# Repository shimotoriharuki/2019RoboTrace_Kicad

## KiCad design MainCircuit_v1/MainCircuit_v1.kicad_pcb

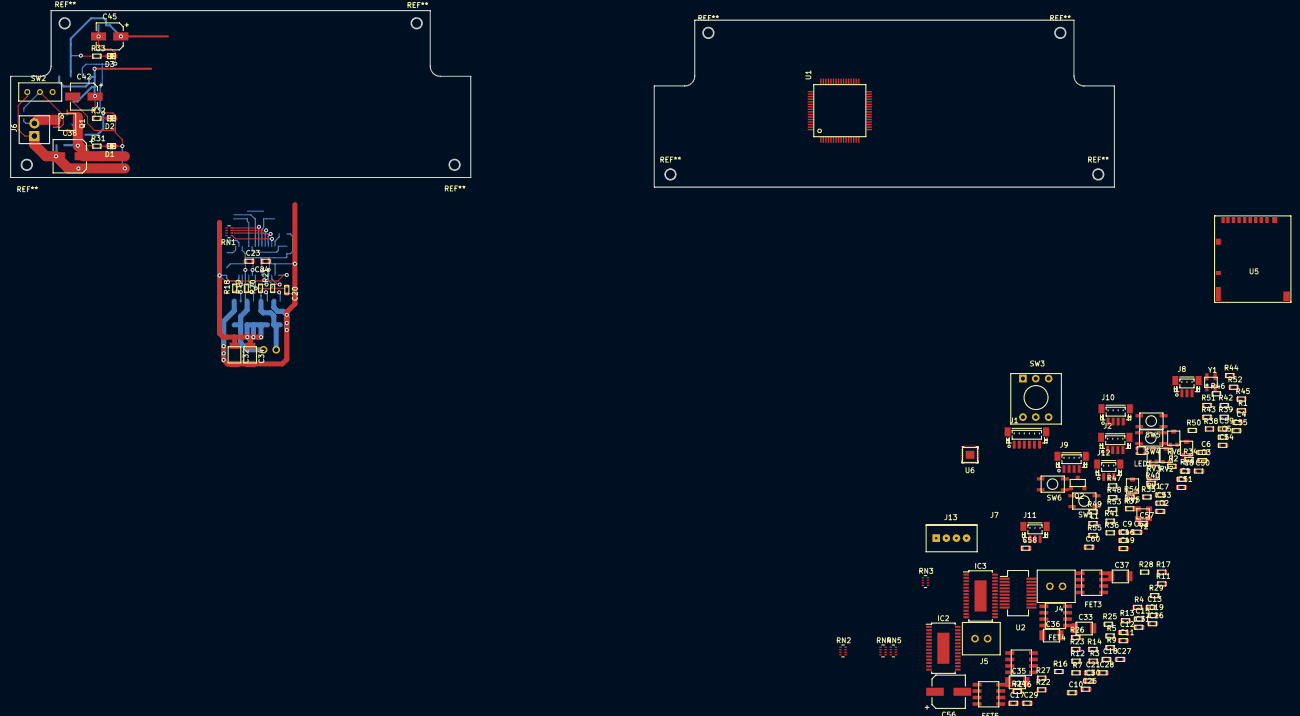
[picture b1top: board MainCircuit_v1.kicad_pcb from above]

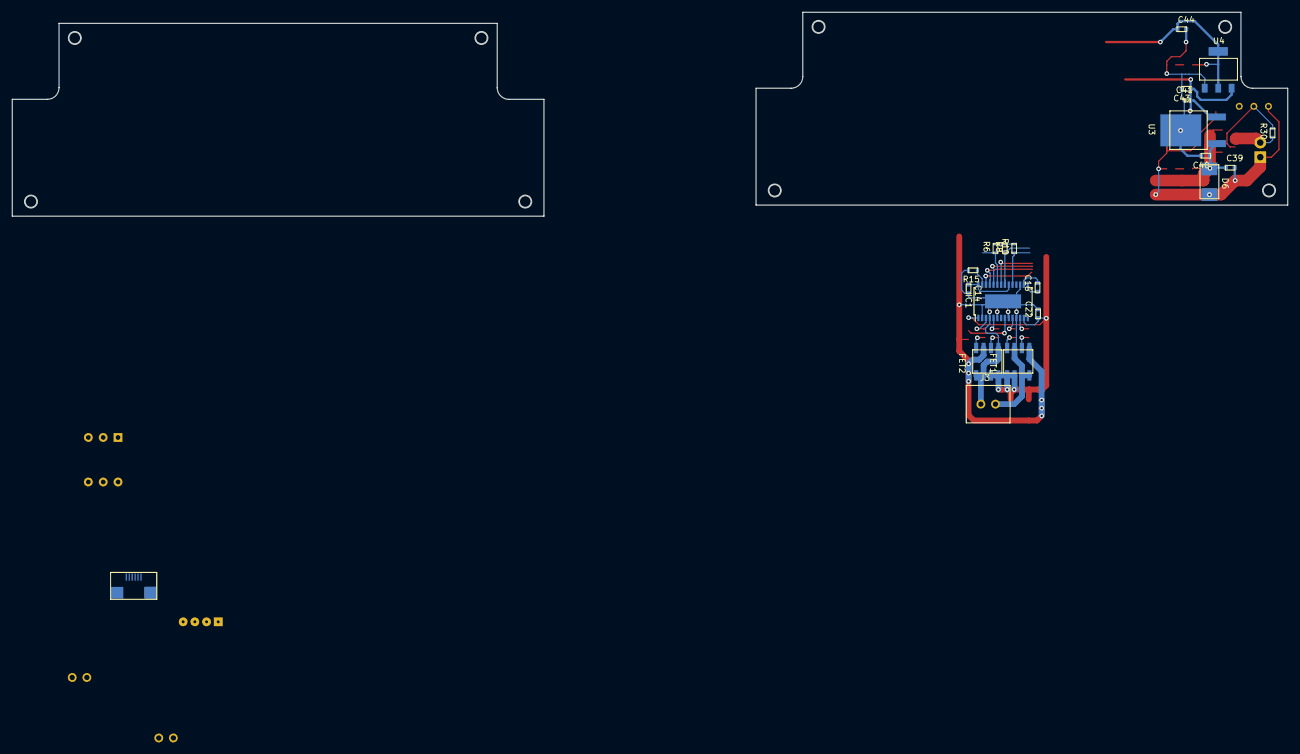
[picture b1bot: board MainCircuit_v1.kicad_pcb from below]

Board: 2 copper layers, 218.3 x 34.9 mm, 168 parts (20 on the bottom side), 139 nets.

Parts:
C1, C3, C4, C5, C6, C8, C9, C10, C11, C12, C13, C14, C15, C18, C52, C54, C55, C57, C58, C59, C60: 0.1u; C_1608_HandSolderring
C2, C39, C43, C44, C49, C50, C51: 1u; C_1608_HandSolderring
C7: 4.7u; C_1608_HandSolderring
C16, C17, C19: 470n; C_1608_HandSolderring
C20, C21, C23, C24, C26, C27, C28, C30, C31: 0.22u; C_1608_HandSolderring
C22, C25, C29: 10u; C_1608_HandSolderring
C32, C33, C34, C35, C36, C37: 47u; c_3225
C38, C56: 180u; CP_Elec_6.3x5.8
C40: 0.39u; C_1608_HandSolderring
C41: 2.2u; c_1005
C42, C45: 82u; CP_Elec_5x5.8
C46: 0.1; C_1608_HandSolderring
C53: 0.1U; C_1608_HandSolderring
D1, D2, D3: LED; LED 1608
D6: 1SMB5930BT3G
FET1, FET2, FET3, FET4, FET5, FET6: IRF8915
IC1, IC2, IC3: A3921; TSSOP-28-1EP_4.4x9.7mm_Pitch0.65mm
J1: SH; JST_SH_BM06B-SRSS-TB_06x1.00mm_Straight
J2, J9, J10: SH; JST_SH_BM04B-SRSS-TB_04x1.00mm_Straight
J3, J4, J5: XA; XA_top_2pin
J6: ILG; ILG_2pin
J7: FFC; CN-FFC-(0.5)6PD
J8, J11, J12: SH; JST_SH_BM03B-SRSS-TB_03x1.00mm_Straight
J13: PA; PA_4pin
L1: 330; R_1608_HandSoldering
LED1: OSTB0603C1C-A
Q1: μPA2815T1S; uPA2815T1S
Q2: DMG3415U
R1: 150k; R_1608_HandSoldering
R2, R3, R4, R5, R6, R7, R8, R9, R10, R11, R12, R13, R14, R34, R35, R36, R37, R38, R39, R43, R45, R47, R53, R54: 10k; R_1608_HandSoldering
R15, R16, R17: 3k; R_1608_HandSoldering
R18, R19, R20, R21, R22, R23, R24, R25, R26, R27, R28, R29: 75; R_1608_HandSoldering
R30: 12K; R_1608_HandSoldering
R31: 1k; R_1608_HandSoldering
R32: 560; R_1608_HandSoldering
R33: 270; R_1608_HandSoldering
R40, R41, R42: 47K; R_1608_HandSoldering
R44, R46, R48: 100; R_1608_HandSoldering
R49: 1.2k; R_1608_HandSoldering
R50: 680; R_1608_HandSoldering
R51: 470; R_1608_HandSoldering
R52: 39; R_1608_HandSoldering
R55: 10K; R_1608_HandSoldering
RN1, RN2, RN3, RN4, RN5: 10k; my_RN
RV1, RV2, RV3, RV4, RV5, RV6: 1k; ST2TA
SW1, SW4, SW5, SW6: SKRPACE010
SW2: SS12D01G4
SW3: ERD216RSZ; rotary_switch
U1: STM32F446RE; stm32f401
U2: ADuM7640; ADUM7640ARQZ
U3: NJM2845; NJM2845DL1
U4: ADP3338; SOT-223
U5: SD_SLOT; micro_SDcard
U6: ICM20648
Y1: ASDMB-8.000MHZ-LY-T
Y2: TC25L5I32K7680

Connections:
+3V3: C1.1, C3.1, C5.2, C6.1, C8.1, C9.1, C10.1, C11.1, C12.1, C13.1, C44.1, C45.1, C46.1, C52.1, C54.1, C55.1, C57.1, C59.1, J1.1, J2.1, J12.1, J13.1, L1.2, LED1.1, Q2.1, R1.1, R33.1, R34.1, R35.1, R36.1, R37.1, R38.1, R39.1, R40.1, R41.1, R42.1, R43.1, R45.1, R47.1, R53.1, R54.1, R55.1, RN1.5, RN1.6, RN1.7, RN1.8, RN2.5, RN2.6, RN2.7, RN2.8, RN3.5, RN3.6, RN3.7, RN3.8, RN4.5, RN4.6, RN4.7, RN4.8, U1.1, U1.19, U1.32, U1.48, U1.64, U2.1, U2.7, U2.14, U2.20, U4.2, U5.4, U6.8, U6.13, Y1.4, Y2.1, Y2.4
+5V: C41.1, C42.1, C43.1, C58.1, C60.1, J9.1, J10.1, R32.1, RN5.5, RN5.6, RN5.7, RN5.8, U3.3, U4.3
+BATT: C22.1, C25.1, C29.1, C32.1, C33.1, C34.1, C35.1, C36.1, C37.1, C38.1, C39.1, C40.1, C56.1, D6.1, FET1.5, FET1.6, FET2.7, FET2.8, FET3.5, FET3.6, FET4.7, FET4.8, FET5.5, FET5.6, FET6.7, FET6.8, IC1.1, IC1.13, IC2.1, IC2.13, IC3.1, IC3.13, Q1.3, R31.1, U3.1
CS_IMU: RN4.1, U1.54, U6.22
CS_SD: U1.50, U5.2
DIR_MAXON1: IC1.19, R10.1, U1.40
DIR_MAXON2: IC2.19, R11.1, U1.36
DIR_VCM: R5.1, U1.45, U2.3
ENCORDER_1A: J9.2, RN5.1, U1.14
ENCORDER_1B: J9.3, RN5.2, U1.15
ENCORDER_2A: J10.2, RN5.4, U1.58
ENCORDER_2B: J10.3, RN5.3, U1.59
GND: C1.2, C2.2, C3.2, C4.1, C5.1, C6.2, C7.2, C8.2, C9.2, C10.2, C11.2, C12.2, C13.2, C14.2, C15.2, C18.2, C20.2, C21.2, C22.2, C25.2, C28.2, C29.2, C32.2, C33.2, C34.2, C35.2, C36.2, C37.2, C38.2, C39.2, C40.2, C41.2, C42.2, C43.2, C44.2, C45.2, C46.2, C49.2, C50.2, C51.2, C52.2, C56.2, C57.2, C58.2, C59.2, C60.2, D1.1, D2.1, D3.1, D6.2, FET1.1, FET2.3, FET3.1, FET4.3, FET5.1, FET6.3, IC1.2, IC1.17, IC1.29, IC2.2, IC2.17, IC2.29, IC3.2, IC3.17, IC3.29, J1.3, J2.4, J6.1, J7.6, J8.3, J9.4, J10.4, J11.3, J12.3, J13.4, R2.1, R3.2, R4.2, R5.2, R6.2, R7.2, R8.2, R9.2, R10.2, R11.2, R12.2, R13.2, R14.2, R15.2, R16.2, R17.2, SW1.1, SW2.3, SW3.C, SW4.2, SW5.2, SW6.2, U1.12, U1.18, U1.31, U1.47, U1.63, U2.2, U2.10, U2.19, U3.2, U4.1, U5.6, U5.9, U5.11, U6.11, U6.18, U6.20, Y1.2, Y2.2
INSERT_SD: R41.2, U1.2, U5.10
LED_B: R51.2, U1.28
LED_G: R50.2, U1.33
LED_R: R49.2, U1.34
LINE_SENSOR1: J7.2, RV1.1, U1.26
LINE_SENSOR2: J7.3, RV2.1, U1.25
LINE_SENSOR3: J7.4, RV3.1, U1.24
LINE_SENSOR4: J7.5, RV4.1, U1.23
LINE_SENSOR5: J8.2, RV5.1, U1.22
LINE_SENSOR6: J11.2, RV6.1, U1.21
MISO_IMU: RN4.4, U1.56, U6.9
MISO_SD: U1.52, U5.7
MOSI_IMU: RN4.3, U1.57, U6.24
MOSI_SD: U1.53, U5.3
NRST: C2.1, J1.5, R1.2, SW1.2, U1.7
unnamed: C4.2, L1.1, U1.13
unnamed: C7.1, U1.30
unnamed: C14.1, IC1.20, IC1.28
unnamed: C15.1, IC2.20, IC2.28
unnamed: C16.1, IC1.15
unnamed: C16.2, IC1.16
unnamed: C17.1, IC2.15
unnamed: C17.2, IC2.16
unnamed: C18.1, IC3.20, IC3.28
unnamed: C19.1, IC3.15
unnamed: C19.2, IC3.16
unnamed: C20.1, IC1.8
unnamed: C21.1, IC2.8
unnamed: C23.1, FET1.3, FET1.7, FET1.8, IC1.11, J3.1
unnamed: C23.2, IC1.9
unnamed: C24.1, FET2.1, FET2.5, FET2.6, IC1.4, J3.2
unnamed: C24.2, IC1.6
unnamed: C26.1, FET3.3, FET3.7, FET3.8, IC2.11, J4.1
unnamed: C26.2, IC2.9
unnamed: C27.1, FET4.1, FET4.5, FET4.6, IC2.4, J4.2
unnamed: C27.2, IC2.6
unnamed: C28.1, IC3.8
unnamed: C30.1, FET5.3, FET5.7, FET5.8, IC3.11, J5.1
unnamed: C30.2, IC3.9
unnamed: C31.1, FET6.1, FET6.5, FET6.6, IC3.4, J5.2
unnamed: C31.2, IC3.6
unnamed: C53.1, U6.10
unnamed: C53.2, C54.2, C55.2
unnamed: D1.2, R31.2
unnamed: D2.2, R32.2
unnamed: D3.2, R33.2
unnamed: FET1.2, R18.1
unnamed: FET1.4, R19.1
unnamed: FET2.2, R20.1
unnamed: FET2.4, R21.1
unnamed: FET3.2, R22.1
unnamed: FET3.4, R23.1
unnamed: FET4.2, R24.1
unnamed: FET4.4, R25.1
unnamed: FET5.2, R26.1
unnamed: FET5.4, R27.1
unnamed: FET6.2, R28.1
unnamed: FET6.4, R29.1
unnamed: IC1.3, R21.2
unnamed: IC1.5, R20.2
unnamed: IC1.10, R19.2
unnamed: IC1.12, R18.2
unnamed: IC1.22, RN1.4
unnamed: IC1.24, RN1.3
unnamed: IC1.25, RN1.2
unnamed: IC1.26, RN1.1
unnamed: IC1.27, R15.1
unnamed: IC2.3, R25.2
unnamed: IC2.5, R24.2
unnamed: IC2.10, R23.2
unnamed: IC2.12, R22.2
unnamed: IC2.22, RN2.4
unnamed: IC2.24, RN2.3
unnamed: IC2.25, RN2.2
unnamed: IC2.26, RN2.1
unnamed: IC2.27, R16.1
unnamed: IC3.3, R29.2
unnamed: IC3.5, R28.2
unnamed: IC3.10, R27.2
unnamed: IC3.12, R26.2
unnamed: IC3.19, R14.1, U2.18
unnamed: IC3.21, R13.1, U2.17
unnamed: IC3.22, RN3.4
unnamed: IC3.23, R12.1, U2.16
unnamed: IC3.24, RN3.3
unnamed: IC3.25, RN3.2
unnamed: IC3.26, RN3.1
unnamed: IC3.27, R17.1
unnamed: J6.2, Q1.1, R30.1
unnamed: J7.1, J8.1, J11.1, Q2.3
unnamed: LED1.2, R49.1
unnamed: LED1.3, R51.1
unnamed: LED1.4, R50.1
unnamed: Q1.2, R30.2, SW2.2
unnamed: Q2.2, R52.1, R55.2
unnamed: R2.2, U1.60
unnamed: R40.2, U5.8
unnamed: R42.2, U5.1
unnamed: R44.1, SW4.1
unnamed: R46.1, SW5.1
unnamed: R48.1, SW6.1
OSC_IN: U1.5, Y1.3
POT: J12.2, U1.27
PWM_MAXON1: IC1.23, R6.1, U1.38
PWM_MAXON2: IC2.23, R7.1, U1.37
PWM_VCM: R3.1, U1.44, U2.5
RTC_IN: U1.3, Y2.3
RX: J2.2, U1.43
R_SW1: SW3.1, U1.8
R_SW2: SW3.2, U1.9
R_SW4: SW3.4, U1.10
R_SW8: SW3.8, U1.11
SCK_IMU: RN4.2, U1.55, U6.23
SCK_SD: U1.51, U5.5
SCL_LCD: J13.2, R53.2, U1.61
SDA_LCD: J13.3, R54.2, U1.62
SENSOR_PULS_PWM: R52.2, U1.29
SR_MAXON1: IC1.21, R8.1, U1.39
SR_MAXON2: IC2.21, R9.1, U1.35
SR_VCM: R4.1, U1.41, U2.4
SW1: C49.1, R43.2, R44.2, U1.16
SW2: C50.1, R45.2, R46.2, U1.17
SW3: C51.1, R47.2, R48.2, U1.20
TCK: J1.2, U1.49
TMS: J1.4, U1.46
TX: J2.3, U1.42

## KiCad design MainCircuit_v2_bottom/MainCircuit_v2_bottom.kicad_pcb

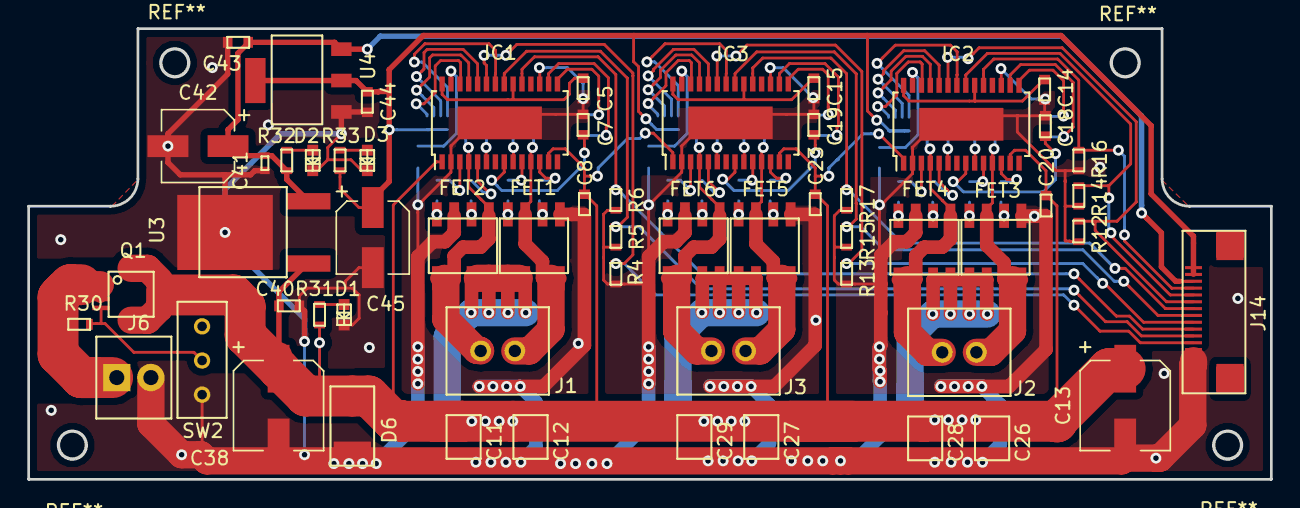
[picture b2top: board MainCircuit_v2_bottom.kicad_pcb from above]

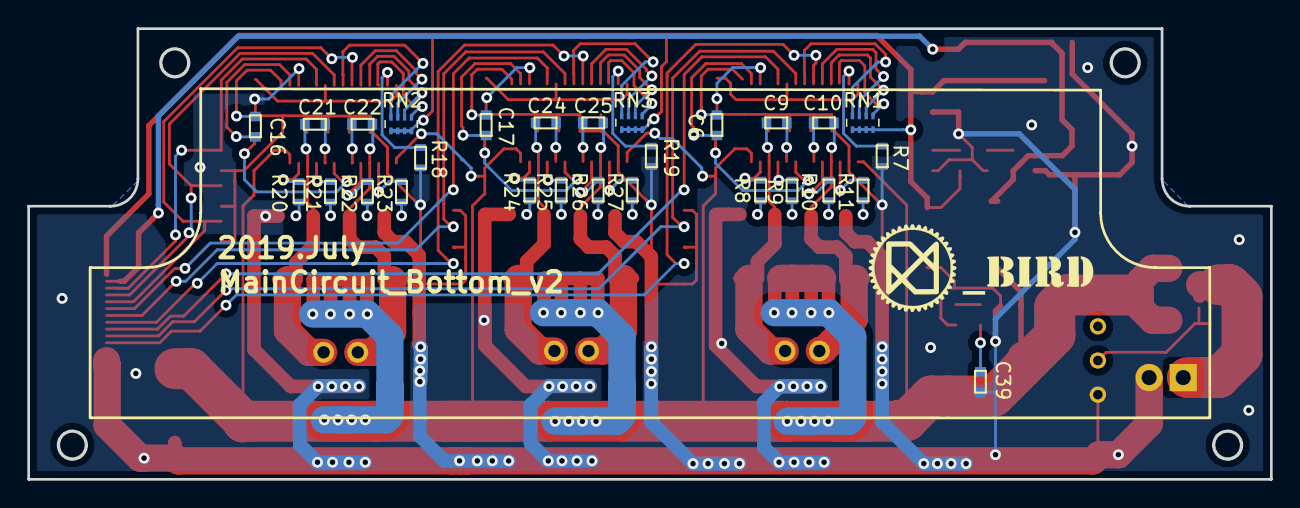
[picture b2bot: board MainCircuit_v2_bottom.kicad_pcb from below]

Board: 2 copper layers, 91.0 x 33.0 mm, 86 parts (29 on the bottom side), 81 nets.

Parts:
C5, C14, C15: 0.1u; C_1608_HandSolderring
C6, C16, C17: 470n; C_1608_HandSolderring
C7, C9, C10, C18, C19, C21, C22, C24, C25: 0.22u; C_1608_HandSolderring
C8, C20, C23: 10u; C_1608_HandSolderring
C11, C12, C26, C27, C28, C29: 47u; c_3225
C13, C38: 180u; CP_Elec_6.3x5.8
C39, C43, C44: 1u; C_1608_HandSolderring
C40: 0.39u; C_1608_HandSolderring
C41: 2.2u; c_1005
C42, C45: 82u; CP_Elec_5x5.8
D1, D2, D3: LED; LED 1608
D6: 1SMB5930BT3G
FET1, FET2, FET3, FET4, FET5, FET6: IRF8915
IC1, IC2, IC3: A3921; TSSOP-28-1EP_4.4x9.7mm_Pitch0.65mm
J1, J2, J3: XA; XA_top_2pin
J6: ILG; ILG_2pin
J14: FFC_to_top; CN-FFC-SMT2(CN-FFC(0.5)14PD)
Q1: μPA2815T1S; uPA2815T1S
R4, R5, R6, R12, R13, R14, R15, R16, R17: 10k; R_1608_HandSoldering
R7, R18, R19: 3k; R_1608_HandSoldering
R8, R9, R10, R11, R20, R21, R22, R23, R24, R25, R26, R27: 75; R_1608_HandSoldering
R30: 12K; R_1608_HandSoldering
R31: 1k; R_1608_HandSoldering
R32: 560; R_1608_HandSoldering
R33: 270; R_1608_HandSoldering
RN1, RN2, RN3: 10k; my_RN
SW2: SS12D01G4
U3: NJM2845; NJM2845DL1
U4: ADP3338; SOT-223

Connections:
+3V3: C44.1, C45.1, J14.1, J14.2, R33.1, RN1.5, RN1.6, RN1.7, RN1.8, RN2.5, RN2.6, RN2.7, RN2.8, RN3.5, RN3.6, RN3.7, RN3.8, U4.2
+5V: C41.1, C42.1, C43.1, J14.3, R32.1, U3.3, U4.3
+BATT: C8.1, C11.1, C12.1, C13.1, C20.1, C23.1, C26.1, C27.1, C28.1, C29.1, C38.1, C39.1, C40.1, D6.1, FET1.5, FET1.6, FET2.7, FET2.8, FET3.5, FET3.6, FET4.7, FET4.8, FET5.5, FET5.6, FET6.7, FET6.8, IC1.1, IC1.13, IC2.1, IC2.13, IC3.1, IC3.13, Q1.3, R31.1, U3.1
DIR_MAXON1_B: IC2.19, J14.4, R16.1
DIR_MAXON2_B: IC3.19, J14.7, R17.1
DIR_VCM_B: IC1.19, J14.10, R6.1
GND: C5.2, C7.2, C8.2, C11.2, C12.2, C13.2, C14.2, C15.2, C18.2, C19.2, C20.2, C23.2, C26.2, C27.2, C28.2, C29.2, C38.2, C39.2, C40.2, C41.2, C42.2, C43.2, C44.2, C45.2, D1.1, D2.1, D3.1, D6.2, FET1.1, FET2.3, FET3.1, FET4.3, FET5.1, FET6.3, IC1.2, IC1.17, IC1.29, IC2.2, IC2.17, IC2.29, IC3.2, IC3.17, IC3.29, J6.2, J14.13, J14.14, R4.2, R5.2, R6.2, R7.2, R12.2, R13.2, R14.2, R15.2, R16.2, R17.2, R18.2, R19.2, SW2.3, U3.2, U4.1
unnamed: C5.1, IC1.20, IC1.28
unnamed: C6.1, IC1.15
unnamed: C6.2, IC1.16
unnamed: C7.1, IC1.8
unnamed: C9.1, FET1.3, FET1.7, FET1.8, IC1.11, J1.1
unnamed: C9.2, IC1.9
unnamed: C10.1, FET2.1, FET2.5, FET2.6, IC1.4, J1.2
unnamed: C10.2, IC1.6
unnamed: C14.1, IC2.20, IC2.28
unnamed: C15.1, IC3.20, IC3.28
unnamed: C16.1, IC2.15
unnamed: C16.2, IC2.16
unnamed: C17.1, IC3.15
unnamed: C17.2, IC3.16
unnamed: C18.1, IC2.8
unnamed: C19.1, IC3.8
unnamed: C21.1, FET3.3, FET3.7, FET3.8, IC2.11, J2.1
unnamed: C21.2, IC2.9
unnamed: C22.1, FET4.1, FET4.5, FET4.6, IC2.4, J2.2
unnamed: C22.2, IC2.6
unnamed: C24.1, FET5.3, FET5.7, FET5.8, IC3.11, J3.1
unnamed: C24.2, IC3.9
unnamed: C25.1, FET6.1, FET6.5, FET6.6, IC3.4, J3.2
unnamed: C25.2, IC3.6
unnamed: D1.2, R31.2
unnamed: D2.2, R32.2
unnamed: D3.2, R33.2
unnamed: FET1.2, R8.1
unnamed: FET1.4, R9.1
unnamed: FET2.2, R10.1
unnamed: FET2.4, R11.1
unnamed: FET3.2, R20.1
unnamed: FET3.4, R21.1
unnamed: FET4.2, R22.1
unnamed: FET4.4, R23.1
unnamed: FET5.2, R24.1
unnamed: FET5.4, R25.1
unnamed: FET6.2, R26.1
unnamed: FET6.4, R27.1
unnamed: IC1.3, R11.2
unnamed: IC1.5, R10.2
unnamed: IC1.10, R9.2
unnamed: IC1.12, R8.2
unnamed: IC1.22, RN1.4
unnamed: IC1.24, RN1.3
unnamed: IC1.25, RN1.2
unnamed: IC1.26, RN1.1
unnamed: IC1.27, R7.1
unnamed: IC2.3, R23.2
unnamed: IC2.5, R22.2
unnamed: IC2.10, R21.2
unnamed: IC2.12, R20.2
unnamed: IC2.22, RN2.4
unnamed: IC2.24, RN2.3
unnamed: IC2.25, RN2.2
unnamed: IC2.26, RN2.1
unnamed: IC2.27, R18.1
unnamed: IC3.3, R27.2
unnamed: IC3.5, R26.2
unnamed: IC3.10, R25.2
unnamed: IC3.12, R24.2
unnamed: IC3.22, RN3.4
unnamed: IC3.24, RN3.3
unnamed: IC3.25, RN3.2
unnamed: IC3.26, RN3.1
unnamed: IC3.27, R19.1
unnamed: J6.1, Q1.1, R30.1
unnamed: Q1.2, R30.2, SW2.2
PWM_MAXON1_B: IC2.23, J14.6, R12.1
PWM_MAXON2_B: IC3.23, J14.9, R13.1
PWM_VCM_B: IC1.23, J14.12, R4.1
SR_MAXON1_B: IC2.21, J14.5, R14.1
SR_MAXON2_B: IC3.21, J14.8, R15.1
SR_VCM_B: IC1.21, J14.11, R5.1

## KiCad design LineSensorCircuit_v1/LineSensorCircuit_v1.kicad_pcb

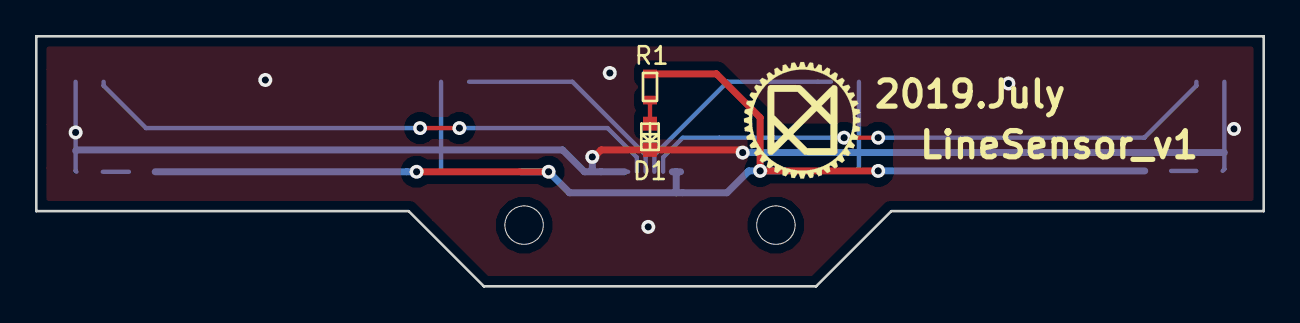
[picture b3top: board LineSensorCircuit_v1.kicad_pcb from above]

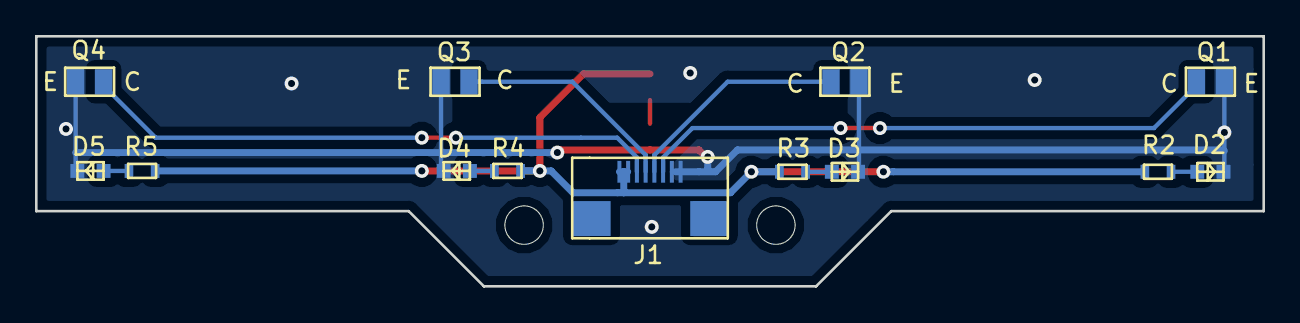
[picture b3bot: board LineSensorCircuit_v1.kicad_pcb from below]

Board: 2 copper layers, 70.2 x 14.3 mm, 15 parts (12 on the bottom side), 11 nets.

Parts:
D1: OSHR1608; LED 1608
D2, D3, D4, D5: SIR19-21C/TR8; SIR19-21C
J1: Conn_01x08; CN-FFC(0.5)8PD
Q1, Q2, Q3, Q4: TEMT7100X01
R1: 330; R_1608_HandSoldering
R2, R3, R4, R5: 39; R_1608_HandSoldering

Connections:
+3V3: J1.7, J1.8, R1.1, R2.1, R3.1, R4.1, R5.1
GND: D1.1, D2.1, D3.1, D4.1, D5.1, J1.1, J1.2, Q1.2, Q2.2, Q3.2, Q4.2
LINE_SENSOR1: J1.6, Q4.1
LINE_SENSOR2: J1.5, Q3.1
LINE_SENSOR3: J1.4, Q2.1
LINE_SENSOR4: J1.3, Q1.1
unnamed: D1.2, R1.2
unnamed: D2.2, R2.2
unnamed: D3.2, R3.2
unnamed: D4.2, R4.2
unnamed: D5.2, R5.2

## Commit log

2022-09-22 init
